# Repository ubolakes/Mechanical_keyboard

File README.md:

[comment]: <> (Author:  Umberto Laghi)
[comment]: <> (Contact: ul2509@gmail.com)
[comment]: <> (Github:  @ubolakes)

# :warning: WORK IN PROGRESS :warning:

# *La Jaderissima* mechanical keyboard

*La Jaderissima* is an open source mechanical keyboard designed with the intent to learn how to design a PCB.  
The repository contains all the materials necessary to build your own *La Jaderissima* at home.

Before introducing the project in more detail, I'd like to thank my friend and colleague, Biagio M., who designed the keyboard case using a 3D CAD software. Without him, I wouldn't have been able to make it.  
He also made the design as thin as possible due to my childish complaints about wanting the keyboard to be as close to the desk as possible.

[comment]: <> (TODO: add image of the final product)

## General overview
The keyboard is designed with a 96% ANSI layout to provide all the necessary keys while reducing the footprint compared to a 100% layout.

<div align="center" style="text-align: center; margin-left: auto; margin-right: auto;">

*Figure 1: Mechanical keyboard layout*
</div>

## Case design
The feature I desire most in a keyboard is a thin design that reduces wrist fatigue without the need for a wrist rest. A slimmer keyboard also offers a sleeker look (I guess).

To achieve this, my friend and colleague, Biagio, designed a bent sheet metal backplate and a 3D-printable bottom case in order to reduce costs and make the keyboard lighter. Biagio also designed 3D-printable feet to angle the keyboard and improve ergonomics.

[comment]: <> (TODO: add render of the two case pieces from CAD)

## Keyswitch
Another design choice that makes the keyboard thinner is the use of low-profile switches. It was difficult to choose the most suitable keyswitch.

The first type of switch I chose was the Kailh Choc. The problem with them is that they are a completely custom design. Finding keycaps, stabilizers, and mechanical drawings to understand the dimensions was difficult and expensive.

After my search, I discovered the Outemu GTMX medium-profile switches. They have a lower profile than Cherry MX switches, but not as low as Kailh Choc switches. They have the same footprint as standard Cherry MX switches and are compatible with MX-specific PCBs, backplates, keycaps, and MX PCB-mounted stabilizers, which allows for a lower price.

<div align="center" style="text-align: center; margin-left: auto; margin-right: auto;">

*Figure 2: Cherry MX and Outemu GTMX heights compared*
</div>

[comment]: <> (TODO: add section with the BOM)

[comment]: <> (TODO: add files  for PCBWAY [and/or AISLER] and Laserboost)

## How to build your own

### PCB
[comment]: <> (TODO: add image of the PCB)

You can build a PCB yourself using the files in the .zip folder, which contains everything the fabricator needs.
You can choose any fabricator, since most of them accept source files exported from KiCAD.

Along with the PCB, you will need hotswap sockets for MX switches. I chose the Kailh ones, but I think these are pretty much standardised.

You will also need diodes to prevent current from flowing in the wrong direction and to avoid unintentional clicks. The specific type of diode required is the 1N4148; these are cheap and easy to obtain.

### Switches
You can mount any type of mechanical switch as long as it is MX compatible.
For the stabilizers, you can choose PCB-mounted or plate-mounted ones, as the PCB has holes for them and the plate is designed to hold stabilizers.

[comment]: <> (TODO: add section about stabs)

### Keycaps
As long as they use an ANSI layout, you can choose any type of keycap.
I chose a low-profile set to maintain a short profile.

### Case
The case can be 3D-printed in any material or color you prefer.
Since I used a standard 3D printer, I had to split the case into two parts to fit the printer's build plate. I used two 4x16 mm plugs and four 3x16 mm plugs to join them; you can also add glue to better keep the pieces together.

If you have access to a 3D printer with a larger footprint, I included a step file so you can print the case in one piece and avoid using plugs.

Since you are a skilled 3D designer, I also included the CAD file of the keyboard PCB with switches so that you can design your own case with all the features you desire.

[comment]: <> (TODO: add CAD files for the case: split version and integral)
[comment]: <> (TODO: add image of the 3d printed case)

### MCU
I decided to use a Raspberry Pi Pico as the MCU for the mechanical keyboard because it's inexpensive, can be mounted using connector pins, and has plenty of GPIO to handle the entire keyboard.
While an original RPi Pico is not necessary, as they could be more expensive, any Chinese clone is fine as long as it has the same pinout and an RP2040 MCU.

### Firmware
[comment]: <> (TODO: add guide on how to flash the firmware)
The firmware was developed using QMK, and it can be flashed on an RP2040 MCU. Otherwise, it would not work.

To compile and flash the firmware on your La_Jaderissima keyboard, you need to install the QMK environment. The following steps are specifically for a GNU/Linux operating system (OS). If you are using a different OS, you can follow the specific guide on the QMK website.

1. Install the QMK CLI
```
curl -fsSL https://install.qmk.fm | sh
```
2. Download the fork containing La_Jaderissima firmware
```
qmk setup ubolakes/La_Jaderissima_qmk_firmware
```
3. Connect the RPi Pico via USB and go into bootloader mode
4. Build and flash the firmware on the MCU
```
qmk flash -kb la_jaderissima -km default
```

If everything worked fine you now have a RPi Pico with La_Jaderissima firmware flashed.

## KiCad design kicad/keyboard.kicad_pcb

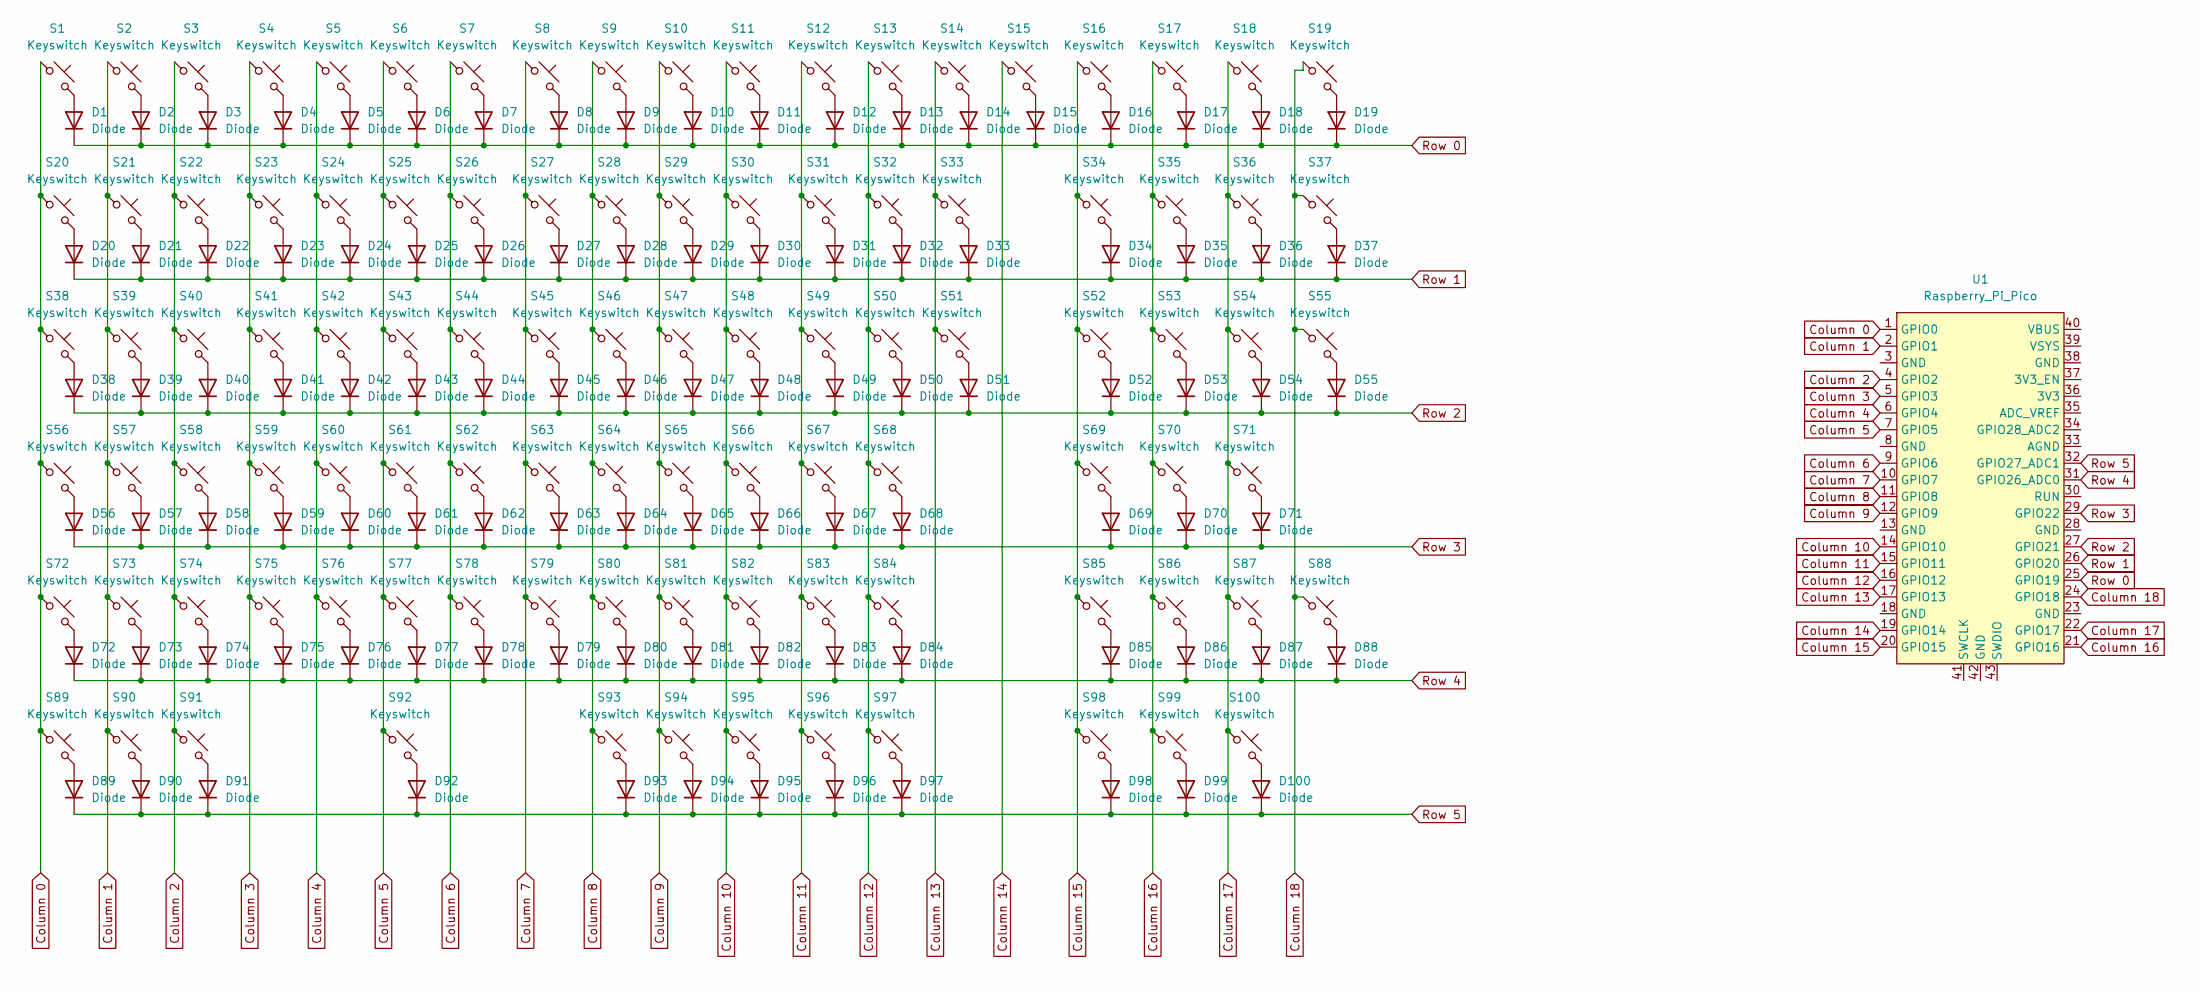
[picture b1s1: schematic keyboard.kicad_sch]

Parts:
D1, D2, D3, D4, D5, D6, D7, D8, D9, D10, D11, D12, D13, D14, D15, D16, D17, D18, D19, D20, D21, D22, D23, D24, D25, D26, D27, D28, D29, D30, D31, D32, D33, D34, D35, D36, D37, D38, D39, D40, D41, D42, D43, D44, D45, D46, D47, D48, D49, D50, D51, D52, D53, D54, D55, D56, D57, D58, D59, D60, D61, D62, D63, D64, D65, D66, D67, D68, D69, D70, D71, D72, D73, D74, D75, D76, D77, D78, D79, D80, D81, D82, D83, D84, D85, D86, D87, D88, D89, D90, D91, D92, D93, D94, D95, D96, D97, D98, D99, D100: Diode; Diode_DO-35
S1, S2, S3, S4, S5, S6, S7, S8, S9, S10, S11, S12, S13, S14, S15, S16, S17, S18, S19, S20, S21, S22, S23, S24, S25, S26, S27, S28, S29, S30, S31, S32, S34, S35, S36, S37, S39, S40, S41, S42, S43, S44, S45, S46, S47, S48, S49, S50, S52, S53, S54, S57, S58, S59, S60, S61, S62, S63, S64, S65, S66, S67, S69, S70, S71, S73, S74, S75, S76, S77, S78, S79, S80, S81, S82, S84, S85, S86, S87, S93, S94, S95, S96, S97, S98, S99, S100: Keyswitch; Hotswap_MX_1.00u
S33: Keyswitch; Hotswap_MX_2.00u
S38, S51: Keyswitch; Hotswap_MX_1.50u
S55, S88: Keyswitch; Hotswap_MX_2.00u_90deg
S56, S83: Keyswitch; Hotswap_MX_1.75u
S68, S72: Keyswitch; Hotswap_MX_2.25u
S89, S90, S91: Keyswitch; Hotswap_MX_1.25u
S92: Keyswitch; Hotswap_MX_6.25u
U1: Raspberry_Pi_Pico

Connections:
Column 0: S1.1, S20.1, S38.1, S56.1, S72.1, S89.1, U1.1 (GPIO0)
Column 1: S2.1, S21.1, S39.1, S57.1, S73.1, S90.1, U1.2 (GPIO1)
Column 2: S3.1, S22.1, S40.1, S58.1, S74.1, S91.1, U1.4 (GPIO2)
Column 3: S4.1, S23.1, S41.1, S59.1, S75.1, U1.5 (GPIO3)
Column 4: S5.1, S24.1, S42.1, S60.1, S76.1, U1.6 (GPIO4)
Column 5: S6.1, S25.1, S43.1, S61.1, S77.1, S92.1, U1.7 (GPIO5)
Column 6: S7.1, S26.1, S44.1, S62.1, S78.1, U1.9 (GPIO6)
Column 7: S8.1, S27.1, S45.1, S63.1, S79.1, U1.10 (GPIO7)
Column 8: S9.1, S28.1, S46.1, S64.1, S80.1, S93.1, U1.11 (GPIO8)
Column 9: S10.1, S29.1, S47.1, S65.1, S81.1, S94.1, U1.12 (GPIO9)
Column 10: S11.1, S30.1, S48.1, S66.1, S82.1, S95.1, U1.14 (GPIO10)
Column 11: S12.1, S31.1, S49.1, S67.1, S83.1, S96.1, U1.15 (GPIO11)
Column 12: S13.1, S32.1, S50.1, S68.1, S84.1, S97.1, U1.16 (GPIO12)
Column 13: S14.1, S33.1, S51.1, U1.17 (GPIO13)
Column 14: S15.1, U1.19 (GPIO14)
Column 15: S16.1, S34.1, S52.1, S69.1, S85.1, S98.1, U1.20 (GPIO15)
Column 16: S17.1, S35.1, S53.1, S70.1, S86.1, S99.1, U1.21 (GPIO16)
Column 17: S18.1, S36.1, S54.1, S71.1, S87.1, S100.1, U1.22 (GPIO17)
Column 18: S19.1, S37.1, S55.1, S88.1, U1.24 (GPIO18)
unnamed: D1.2 (A), S1.2
unnamed: D2.2 (A), S2.2
unnamed: D3.2 (A), S3.2
unnamed: D4.2 (A), S4.2
unnamed: D5.2 (A), S5.2
unnamed: D6.2 (A), S6.2
unnamed: D7.2 (A), S7.2
unnamed: D8.2 (A), S8.2
unnamed: D9.2 (A), S9.2
unnamed: D10.2 (A), S10.2
unnamed: D11.2 (A), S11.2
unnamed: D12.2 (A), S12.2
unnamed: D13.2 (A), S13.2
unnamed: D14.2 (A), S14.2
unnamed: D15.2 (A), S15.2
unnamed: D16.2 (A), S16.2
unnamed: D17.2 (A), S17.2
unnamed: D18.2 (A), S18.2
unnamed: D19.2 (A), S19.2
unnamed: D20.2 (A), S20.2
unnamed: D21.2 (A), S21.2
unnamed: D22.2 (A), S22.2
unnamed: D23.2 (A), S23.2
unnamed: D24.2 (A), S24.2
unnamed: D25.2 (A), S25.2
unnamed: D26.2 (A), S26.2
unnamed: D27.2 (A), S27.2
unnamed: D28.2 (A), S28.2
unnamed: D29.2 (A), S29.2
unnamed: D30.2 (A), S30.2
unnamed: D31.2 (A), S31.2
unnamed: D32.2 (A), S32.2
unnamed: D33.2 (A), S33.2
unnamed: D34.2 (A), S34.2
unnamed: D35.2 (A), S35.2
unnamed: D36.2 (A), S36.2
unnamed: D37.2 (A), S37.2
unnamed: D38.2 (A), S38.2
unnamed: D39.2 (A), S39.2
unnamed: D40.2 (A), S40.2
unnamed: D41.2 (A), S41.2
unnamed: D42.2 (A), S42.2
unnamed: D43.2 (A), S43.2
unnamed: D44.2 (A), S44.2
unnamed: D45.2 (A), S45.2
unnamed: D46.2 (A), S46.2
unnamed: D47.2 (A), S47.2
unnamed: D48.2 (A), S48.2
unnamed: D49.2 (A), S49.2
unnamed: D50.2 (A), S50.2
unnamed: D51.2 (A), S51.2
unnamed: D52.2 (A), S52.2
unnamed: D53.2 (A), S53.2
unnamed: D54.2 (A), S54.2
unnamed: D55.2 (A), S55.2
unnamed: D56.2 (A), S56.2
unnamed: D57.2 (A), S57.2
unnamed: D58.2 (A), S58.2
unnamed: D59.2 (A), S59.2
unnamed: D60.2 (A), S60.2
unnamed: D61.2 (A), S61.2
unnamed: D62.2 (A), S62.2
unnamed: D63.2 (A), S63.2
unnamed: D64.2 (A), S64.2
unnamed: D65.2 (A), S65.2
unnamed: D66.2 (A), S66.2
unnamed: D67.2 (A), S67.2
unnamed: D68.2 (A), S68.2
unnamed: D69.2 (A), S69.2
unnamed: D70.2 (A), S70.2
unnamed: D71.2 (A), S71.2
unnamed: D72.2 (A), S72.2
unnamed: D73.2 (A), S73.2
unnamed: D74.2 (A), S74.2
unnamed: D75.2 (A), S75.2
unnamed: D76.2 (A), S76.2
unnamed: D77.2 (A), S77.2
unnamed: D78.2 (A), S78.2
unnamed: D79.2 (A), S79.2
unnamed: D80.2 (A), S80.2
unnamed: D81.2 (A), S81.2
unnamed: D82.2 (A), S82.2
unnamed: D83.2 (A), S83.2
unnamed: D84.2 (A), S84.2
unnamed: D85.2 (A), S85.2
unnamed: D86.2 (A), S86.2
unnamed: D87.2 (A), S87.2
unnamed: D88.2 (A), S88.2
unnamed: D89.2 (A), S89.2
unnamed: D90.2 (A), S90.2
unnamed: D91.2 (A), S91.2
unnamed: D92.2 (A), S92.2
unnamed: D93.2 (A), S93.2
unnamed: D94.2 (A), S94.2
unnamed: D95.2 (A), S95.2
unnamed: D96.2 (A), S96.2
unnamed: D97.2 (A), S97.2
unnamed: D98.2 (A), S98.2
unnamed: D99.2 (A), S99.2
unnamed: D100.2 (A), S100.2
Row 0: D1.1 (K), D2.1 (K), D3.1 (K), D4.1 (K), D5.1 (K), D6.1 (K), D7.1 (K), D8.1 (K), D9.1 (K), D10.1 (K), D11.1 (K), D12.1 (K), D13.1 (K), D14.1 (K), D15.1 (K), D16.1 (K), D17.1 (K), D18.1 (K), D19.1 (K), U1.25 (GPIO19)
Row 1: D20.1 (K), D21.1 (K), D22.1 (K), D23.1 (K), D24.1 (K), D25.1 (K), D26.1 (K), D27.1 (K), D28.1 (K), D29.1 (K), D30.1 (K), D31.1 (K), D32.1 (K), D33.1 (K), D34.1 (K), D35.1 (K), D36.1 (K), D37.1 (K), U1.26 (GPIO20)
Row 2: D38.1 (K), D39.1 (K), D40.1 (K), D41.1 (K), D42.1 (K), D43.1 (K), D44.1 (K), D45.1 (K), D46.1 (K), D47.1 (K), D48.1 (K), D49.1 (K), D50.1 (K), D51.1 (K), D52.1 (K), D53.1 (K), D54.1 (K), D55.1 (K), U1.27 (GPIO21)
Row 3: D56.1 (K), D57.1 (K), D58.1 (K), D59.1 (K), D60.1 (K), D61.1 (K), D62.1 (K), D63.1 (K), D64.1 (K), D65.1 (K), D66.1 (K), D67.1 (K), D68.1 (K), D69.1 (K), D70.1 (K), D71.1 (K), U1.29 (GPIO22)
Row 4: D72.1 (K), D73.1 (K), D74.1 (K), D75.1 (K), D76.1 (K), D77.1 (K), D78.1 (K), D79.1 (K), D80.1 (K), D81.1 (K), D82.1 (K), D83.1 (K), D84.1 (K), D85.1 (K), D86.1 (K), D87.1 (K), D88.1 (K), U1.31 (GPIO26_ADC0)
Row 5: D89.1 (K), D90.1 (K), D91.1 (K), D92.1 (K), D93.1 (K), D94.1 (K), D95.1 (K), D96.1 (K), D97.1 (K), D98.1 (K), D99.1 (K), D100.1 (K), U1.32 (GPIO27_ADC1)

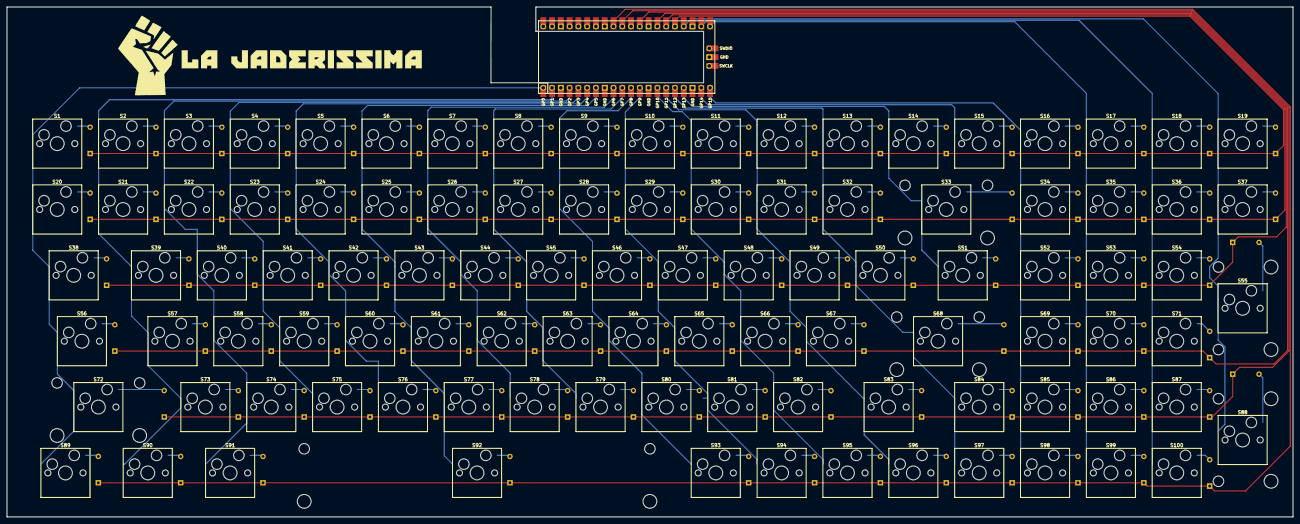
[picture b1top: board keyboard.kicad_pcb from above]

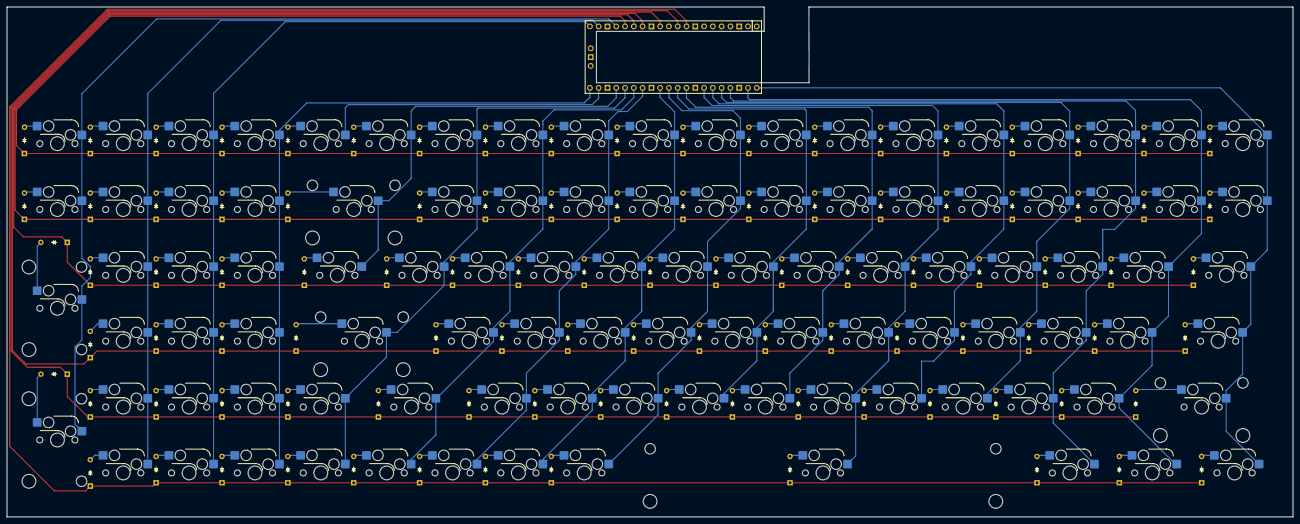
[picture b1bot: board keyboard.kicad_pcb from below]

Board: 2 copper layers, 372.0 x 147.5 mm, 201 parts (100 on the bottom side), 125 nets.

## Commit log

2025-10-26 Uploaded layout of the keyboard
2025-10-26 Uploaded initial design
2025-10-27 Updated design for Kailh Choc V2 switches
2025-11-02 Revert "Updated design for Kailh Choc V2 switches"
    This reverts commit c061ce008c33d35abb33246c03603d5898ebf8bb.
2025-11-02 Updated json layout file
2025-11-02 Uploaded keyboard backplate dxf file
2025-11-06 Updated PCB with the Raspberry Pi Pico as MCU; connected all the rows and columns to the MCU
2025-11-06 Uploaded library containing logos
2025-11-06 Updated PCB with logo
2025-11-09 Updated backplate dxf file with new keyswitch holes
2025-11-09 Uploaded the STEP file of the keyboard pcb
2025-11-09 Uploaded STEP file of the backplate
2025-11-12 Updated PCB design with a different MCU mount in order to reduce the total height
2025-11-12 Updated the PCB design
2025-11-12 Updated STEP file of the PCB
2025-11-15 Reorganized the directories
2025-11-16 Updated PCB design
2025-11-22 Updated README file with a description of the project
2025-11-29 Updated backplate design
2025-12-02 Updated README file with a guide on how to build your own La_Jaderissima
2025-12-02 Uploaded zip folder containing files for the PCB fabricator
2025-12-02 Updated README to center images
2025-12-02 Updated the Case Design chapter
2025-12-04 Uploaded CAD models for the case and feet

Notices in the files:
README.md:
Apache 2.0 license
